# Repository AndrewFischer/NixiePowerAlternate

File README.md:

# NixiePowerAlternate
A regulated power supply for devices with a Nixie tube display.  
Vin is 9 to 14VDC.  Maximum input voltage is 16.5V. 
Outputs are 175VDC, 5VDC and 3.3VDC.<br>
MAX1771 maximum input is 16.5V which sets the upper limit on Vin.
TPS5430 and MAX1771 are inexpensive parts with reasonable performace. There are newer parts with better specs. Most are currently unavailable or beyond my ability to solder.
The TPS5430 is sensitive to choice of output capacitor. See the datasheet and application notes if you stray from the BOM.
#### Rev 0.1 Changes
* Improve HV boost regulator circuit.
* Correct footprint errors in Rev. 0. 
* Replace linear 5.0V regulator with a TPS5430 buck regulator.  Power the 3.3V regulator from the 5V supply. 

### Disclaimers and warnings
:exclamation: Danger of electric shock. 175Volts DC is present on this board.<br>
The files embodied in this repository are provided to you "as-is" and without warranty of any kind, express, implied or otherwise, including without limitation, any warranty of fitness for a particular purpose. See section 5 of the license.<br>
**This project is untested**.<br>
### License
[cc-by-nc 4.0](LICENSE.md)

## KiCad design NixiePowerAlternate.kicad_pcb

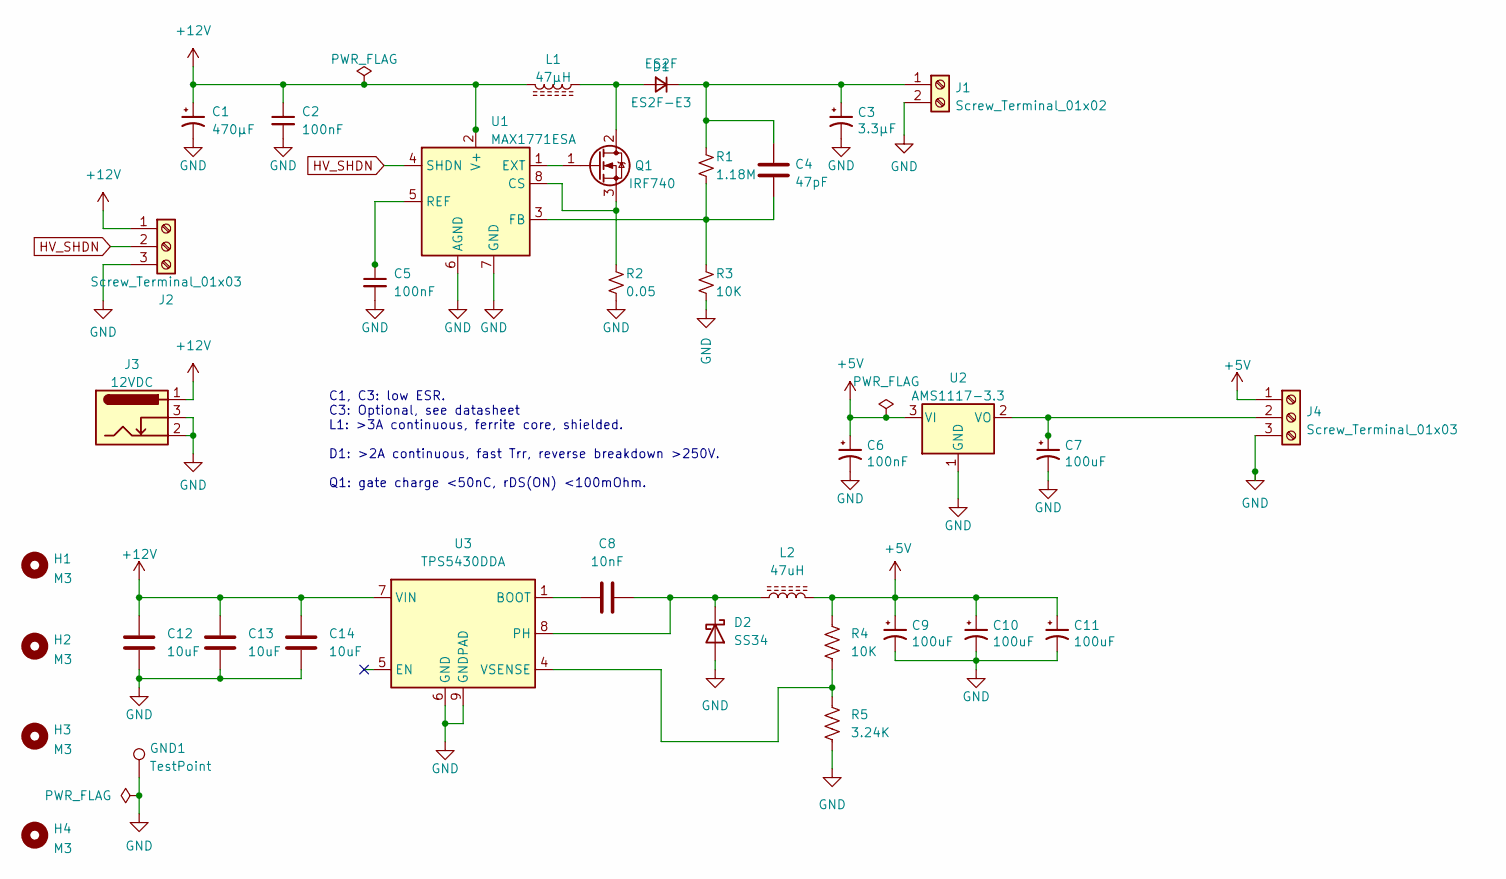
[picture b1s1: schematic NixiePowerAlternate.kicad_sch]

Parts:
C1: 470µF; CP_Radial_D10.0mm_P5.00mm; MPN UPW1V471MPD
C2, C5: 100nF; C_0805_2012Metric; Part# CL21B104KCFNNNE; LCSC C28233
C3: 3.3µF; CP_Radial_D10.0mm_P5.00mm; Part# UPW2G3R3MPD
C4: 47pF; C_1206_3216Metric_Pad1.33x1.80mm_HandSolder; MPN CC1206JRNPOBBN470; LCSC C113890
C6: 100nF; C_0805_2012Metric_Pad1.18x1.45mm_HandSolder; MPN CL21B104KBFNNNE; LCSC C28233
C7, C9, C10, C11: 100uF; CP_EIA-3528-21_Kemet-B_Pad1.50x2.35mm_HandSolder; MPN TAJB107K006RNJ; LCSC C16133
C8: 10nF; C_0805_2012Metric_Pad1.18x1.45mm_HandSolder; MPN CL21B103KBANNNC; LCSC C1710
C12, C13, C14: 10uF; C_1206_3216Metric_Pad1.33x1.80mm_HandSolder; MPN CL31A226KAHNNNE; LCSC C12891
D1: ES2F; D_SMB; MPN ES2F-E3; LCSC C145321
D2: SS34; D_SMA_Handsoldering; MPN SS34; LCSC C8678
GND1: TestPoint; TestPoint_THTPad_D4.0mm_Drill2.0mm
H1, H2, H3, H4: M3; MountingHole_3.2mm_M3
J1: Screw_Terminal_01x02; TerminalBlock_Phoenix_MKDS-1,5-2-5.08_1x02_P5.08mm_Horizont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
J2, J4: Screw_Terminal_01x03; TerminalBlock_Phoenix_MKDS-1,5-3-5.08_1x03_P5.08mm_Horizont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
J3: 12VDC; BarrelJack_RS_805-1696
L1: 47µH; L_CoilCraft_MSS1210; MPN MSS1210H-473ME
L2: 47uH; L_CoilCraft_MSS1048; MPN MSS1048-473MLB
Q1: TO-263-2; MPN IRF740; LCSC C39238
R1: 1.18M; R_1206_3216Metric_Pad1.30x1.75mm_HandSolder; Part# 1206W4F1184T5E; LCSC C422598
R2: 0.05; R_1206_3216Metric_Pad1.30x1.75mm_HandSolder; MPN CR1206FR050P05R; LCSC C149662
R3, R4: 10K; R_0805_2012Metric_Pad1.20x1.40mm_HandSolder; LCSC C17828
R5: 3.24K; R_0805_2012Metric_Pad1.20x1.40mm_HandSolder; MPN CR0805F3K24P05Z; LCSC C245320
U1: MAX1771ESA; SO-8_3.9x4.9mm_P1.27mm; LCSC C407903
U2: AMS1117-3.3; SOT-223-3_TabPin2; LCSC C6186
U3: TPS5430DDA; TI_SO-PowerPAD-8_ThermalVias; LCSC C9864

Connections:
+5V: C6.1, C9.1, C10.1, C11.1, J4.1, L2.2, R4.1, U2.3 (VI)
+12V: C1.1, C2.1, C12.1, C13.1, C14.1, J2.1, J3.1, L1.2, U1.2 (V+), U3.7 (VIN)
GND: C1.2, C2.2, C3.2, C5.2, C6.2, C7.2, C9.2, C10.2, C11.2, C12.2, C13.2, C14.2, D2.2 (A), GND1.1, J1.2, J2.3, J3.2, J3.3, J4.3, R2.2, R3.2, R5.2, U1.6 (AGND), U1.7 (GND), U2.1 (GND), U3.6 (GND), U3.9 (GNDPAD)
HV_SHDN: J2.2, U1.4 (SHDN)
unnamed: C3.1, C4.1, D1.1 (K), J1.1, R1.1
unnamed: C4.2, R1.2, R3.1, U1.3 (FB)
unnamed: C5.1, U1.5 (REF)
unnamed: C7.1, J4.2, U2.2 (VO)
unnamed: C8.1, U3.1 (BOOT)
unnamed: C8.2, D2.1 (K), L2.1, U3.8 (PH)
unnamed: D1.2 (A), L1.1, Q1.2 (D)
unnamed: Q1.1 (G), U1.1 (EXT)
unnamed: Q1.3 (S), R2.1, U1.8 (CS)
unnamed: R4.2, R5.1, U3.4 (VSENSE)

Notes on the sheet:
C1, C3: low ESR. C3: Optional, see datasheet L1: >3A continuous, ferrite core, shielded. D1: >2A continuous, fast Trr, reverse breakdown >250V. Q1: gate charge <50nC, rDS(ON) <100mOhm.

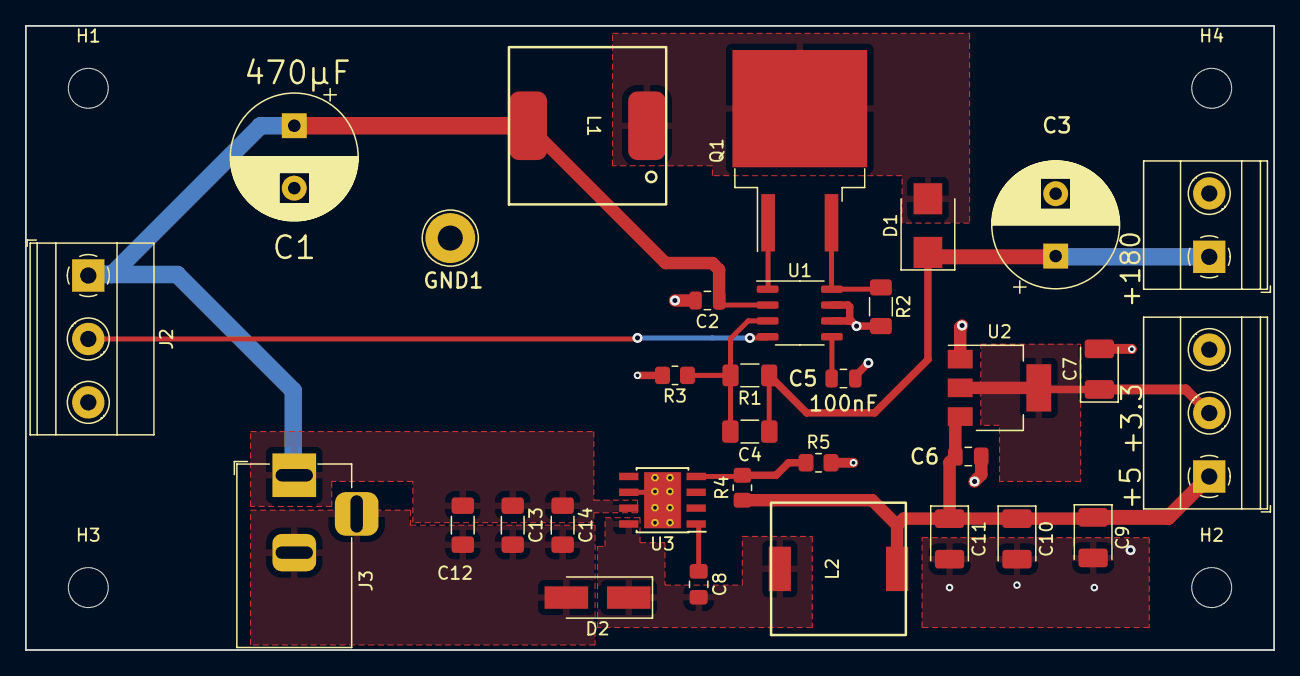
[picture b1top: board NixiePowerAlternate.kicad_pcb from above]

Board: 2 copper layers, 100.0 x 50.0 mm, 36 parts (0 on the bottom side), 14 nets.

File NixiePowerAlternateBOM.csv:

Comment,Designator,Footprint,LCSC
10uF,"C12,C13,C14",Capacitor_SMD:C_1206_3216Metric_Pad1.33x1.80mm_HandSolder,C12891
100nF,"C2,C5",Capacitor_SMD:C_0805_2012Metric,C28233
47pF,C4,Capacitor_SMD:C_1206_3216Metric_Pad1.33x1.80mm_HandSolder,C113890
100nF,C6,Capacitor_SMD:C_0805_2012Metric_Pad1.18x1.45mm_HandSolder,C28233
100uF,"C7,C9,C10,C11",Capacitor_Tantalum_SMD:CP_EIA-3528-21_Kemet-B_Pad1.50x2.35mm_HandSolder,C16133
10nF,C8,Capacitor_SMD:C_0805_2012Metric_Pad1.18x1.45mm_HandSolder,C1710
ES2F,D1,Diode_SMD:D_SMB,C145321
SS34,D2,Diode_SMD:D_SMA_Handsoldering,C8678
~,Q1,Package_TO_SOT_SMD:TO-263-2,C39238
1.18M,R1,Resistor_SMD:R_1206_3216Metric_Pad1.30x1.75mm_HandSolder,C422598
0.05,R2,Resistor_SMD:R_1206_3216Metric_Pad1.30x1.75mm_HandSolder,C149662
10K,"R3,R4",Resistor_SMD:R_0805_2012Metric_Pad1.20x1.40mm_HandSolder,C17828
3.24K,R5,Resistor_SMD:R_0805_2012Metric_Pad1.20x1.40mm_HandSolder,C245320
MAX1771ESA,U1,Package_SO:SO-8_3.9x4.9mm_P1.27mm,C407903
AMS1117-3.3,U2,Package_TO_SOT_SMD:SOT-223-3_TabPin2,C6186
TPS5430DDA,U3,Package_SO:TI_SO-PowerPAD-8_ThermalVias,C9864

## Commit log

2023-02-06 Create LICENSE.md
    Creative Commons Attribution-NonCommercial-ShareAlike 4.0 International
2023-02-06 Add files via upload
    Initial commit for Rev 0.
    Rev 0 has issues and should not be used as is.
2023-02-07 Add files via upload
    Checked L1 and Q1 against recommendations in the datasheet. Decided to keep as is. The MOSFET is fine. L1 should be too and it is rated for 400V.
    Added feed forward capacitor C9, 47pF in parallel with R2. The datasheet suggests values between 47pF and 220pF, using the lowest that insures stability. The design is stable in PSPICE without the ca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
    Updated the PCB with the parts changes and fixed a layout error from Rev 0.
2023-02-08 Add files via upload
    Replace linear 5V regulator with a buck SMPS in the schematic.
    Begin adding MSS1048 footprint
2023-02-09 Add files via upload
    Need to reduce cost before submitting for production.
2023-02-09 Add files via upload
    Rev. 0.1 sent for fabriction. Ready to merge back into main.
2023-02-21 Start converting to KiCad 7
2023-02-21 Schematic cleanup
    Schematic now passes version 7 rules check.
2023-03-31 Better organisation. Add Disclaimer
